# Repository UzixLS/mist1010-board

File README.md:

## MIST.1010
10x10cm PCB variant of [MIST FPGA](https://github.com/mist-devel/mist-board/wiki) project

[[More photos]](images/README.md)

Tech specs:
- EP3C25E144 FPGA
- 32/64Mb SDRAM
- VGA/RGB video output
- Composite video + audio output via 3.5 jack connector (raspberry-pi compatible pinout)
- 4xUSB ports for keyboard, mouse and joysticks
- 2xDB-9 ports for Amiga mouse and joysticks
- SD/microSD card slot
- RTC (clock) with battery
- Tape input / output
- ESP8266 WiFi module
- MIDI input and output (starting from rev.C)
- Type C (starting from rev.D) or MicroUSB power supply
- Board optimized for G738 and G706 cases

Some random photos: [link](https://cloud.err200.net/index.php/s/73TR85tYZkMm8Ax?path=%2Fmist1010)

### Changelog
* Rev.A - first revision. Please note the [errata](pcb/rev.A/ERRATA.txt).
* Rev.A1:
    * fixed all rev.A issues
    * LM3940IS-3.3 replaced to NCP1117-3.3
    * sound output circuit has been replaced with the original one from the MIST 1.3 circuit
    * C39, C40, C80 tantalum capacitors has been replaced by aluminum electrolytic capacitors
    * added ARM's "erase" testpoint
    * removed useless internal speaker
* Rev.A2:
	* C41, C68, C69 10uf ceramic capacitors has been replaced with 22uf tantalum
    * added C74 ceramic capacitor near ESP-01 module
* Rev.B:
    * added ESP-12E/F footprint (ESP-01 is still an option)
    * added MIDI input and output
    * removed U11 - AD724 encoder
    * added resistors-based CVBS (Y+C) video circuit
    * added JP4 solder jumper to disconnect CVBS circuit from 3.5mm jack
    * added U16 buffer with dedicated power source U17 for audio 1-bit DAC
    * added USB 2.54mm header
    * tuned SDRAM traces length for better match with MIST v1.3 PCB
    * changed U6 (attiny) footprint from DIP to SOIC
    * changed Y1 and Y2 footprints from THT to SMD
    * changed 1117-3.3 footprint from TO-252-2 to SOT-223-3
    * added U12 dedicated +3.3V power source for SD card and WiFi
    * 3mm front leds replaced by 5mm
    * R38 (VGA's +5V 0Ω resistor) has been replaced by solder jumper
    * changed tape header pinout
    * pcb corners are rounded now
    * experimental reset circuit based on MAX809
    * various changes in board layout
* Rev.C:
    * used USB Type C instead of Micro USB
    * PJ-320 3.5mm jack replaced by PJ-322
    * added solder jumper to select 3.5mm jack CVBS pinout
    * improved power distribution for FPGA chip
    * removed U16 buffer for DAC as it didn't bring any benefits
    * marked C27 and C28 as DNP
    * reverted to old reset circuit
    * various minor changes in board layout
* Rev.C1:
    * changed R47 from 220Ω to 1kΩ to reduce power led brightness
    * slightly moved C87 and C89

### Useful links
* MIST wiki: [link](https://github.com/mist-devel/mist-board/wiki)
* MIST cores and firmwares: [link](https://github.com/mist-devel/mist-binaries)

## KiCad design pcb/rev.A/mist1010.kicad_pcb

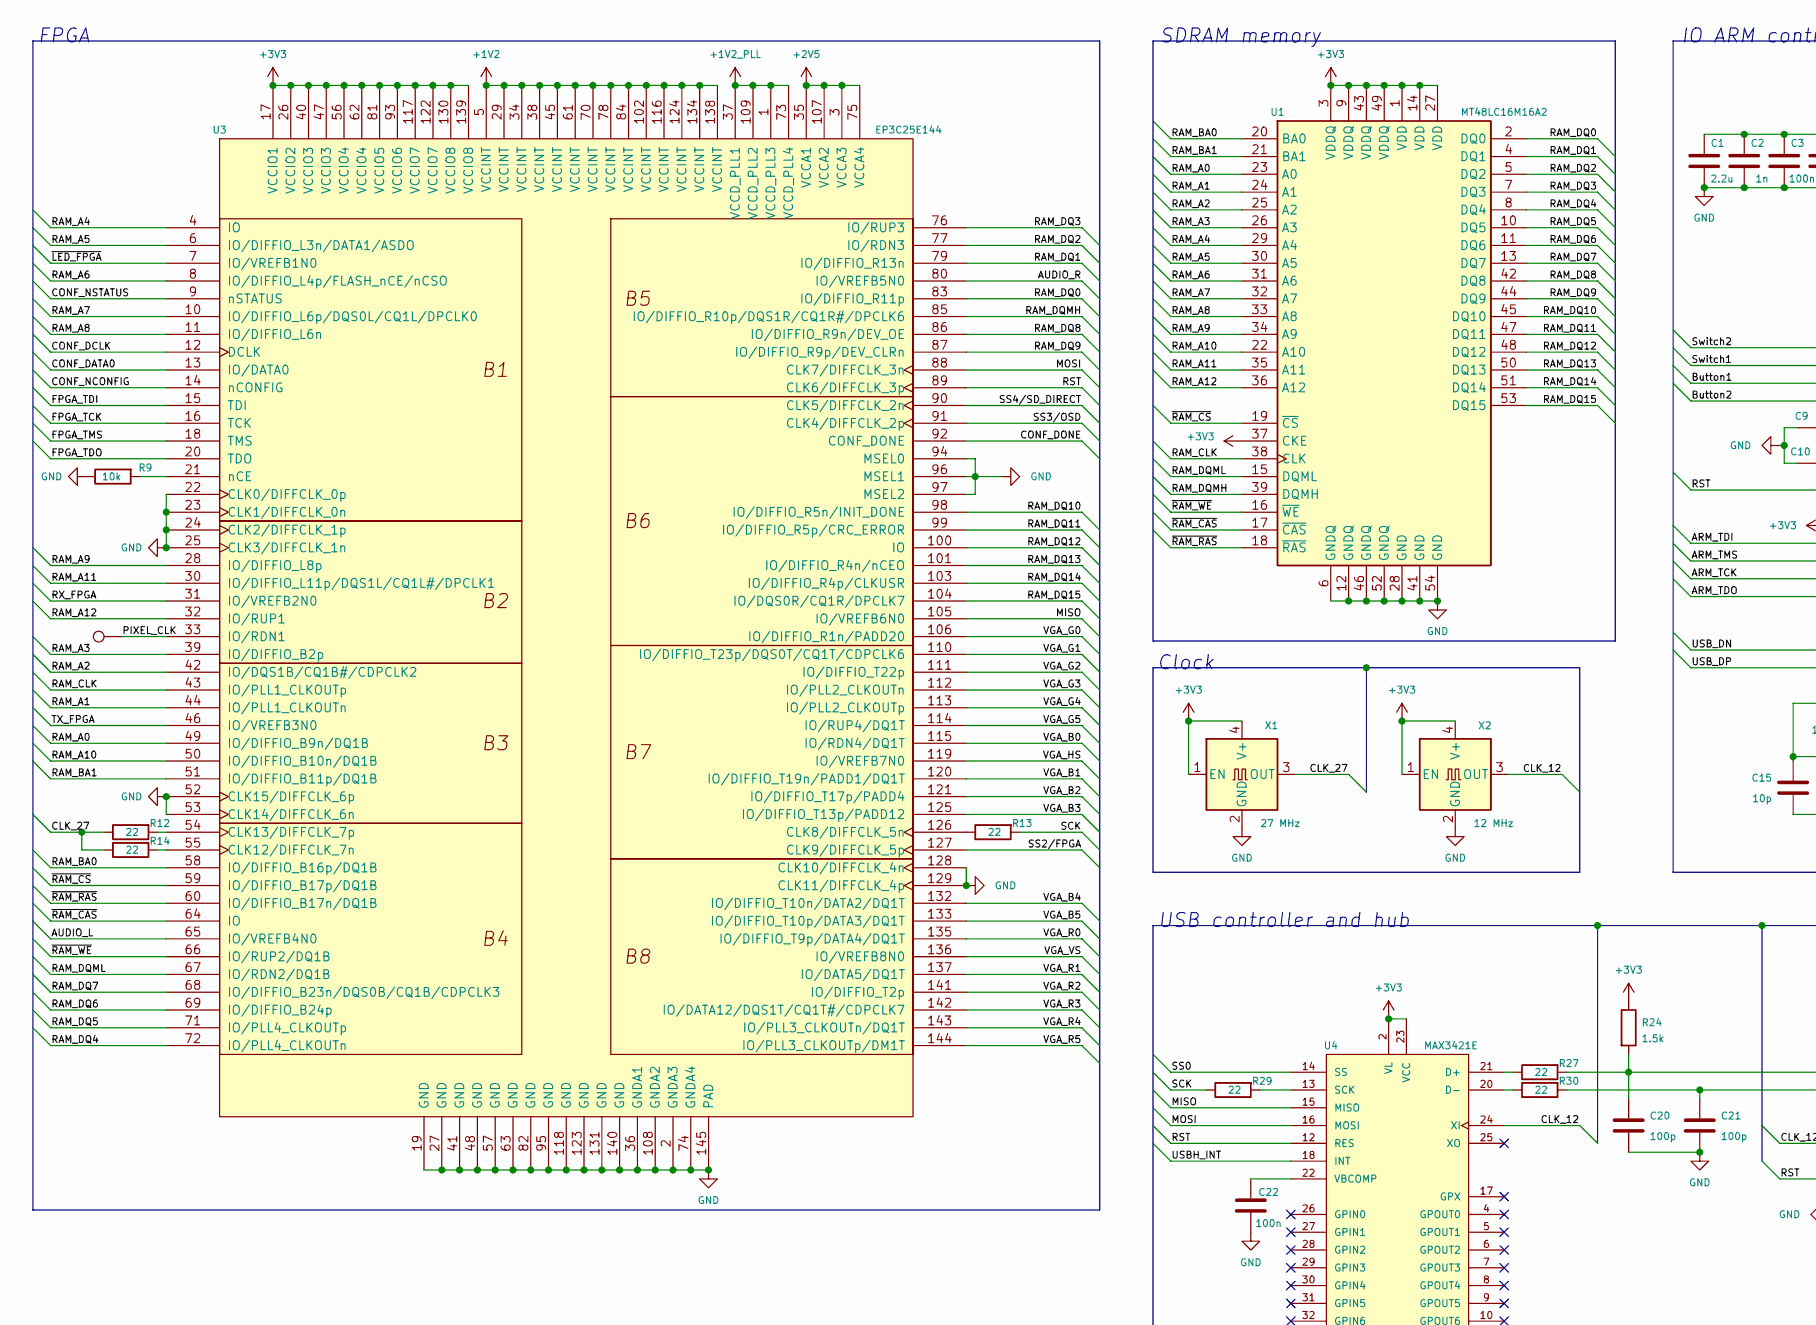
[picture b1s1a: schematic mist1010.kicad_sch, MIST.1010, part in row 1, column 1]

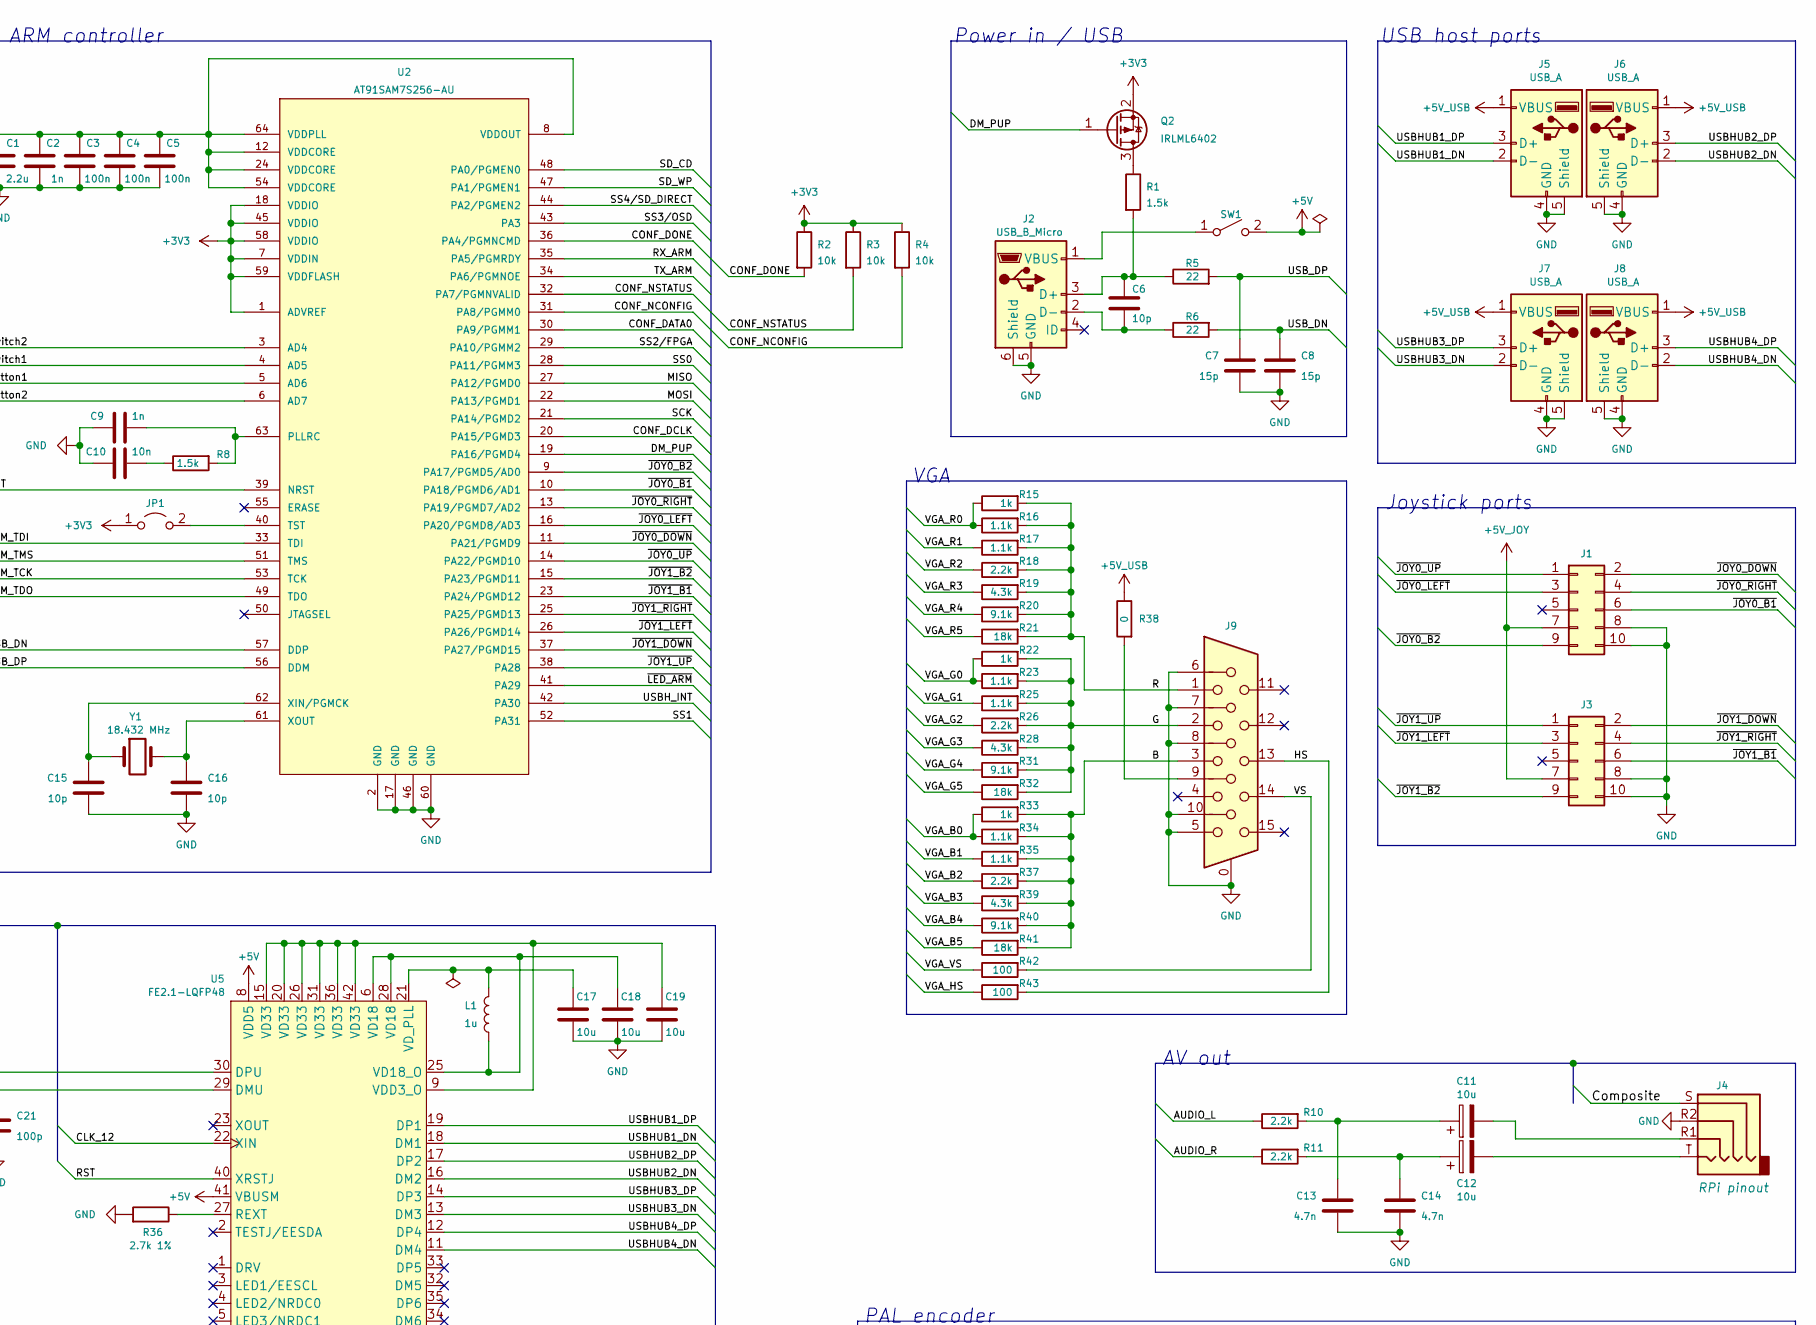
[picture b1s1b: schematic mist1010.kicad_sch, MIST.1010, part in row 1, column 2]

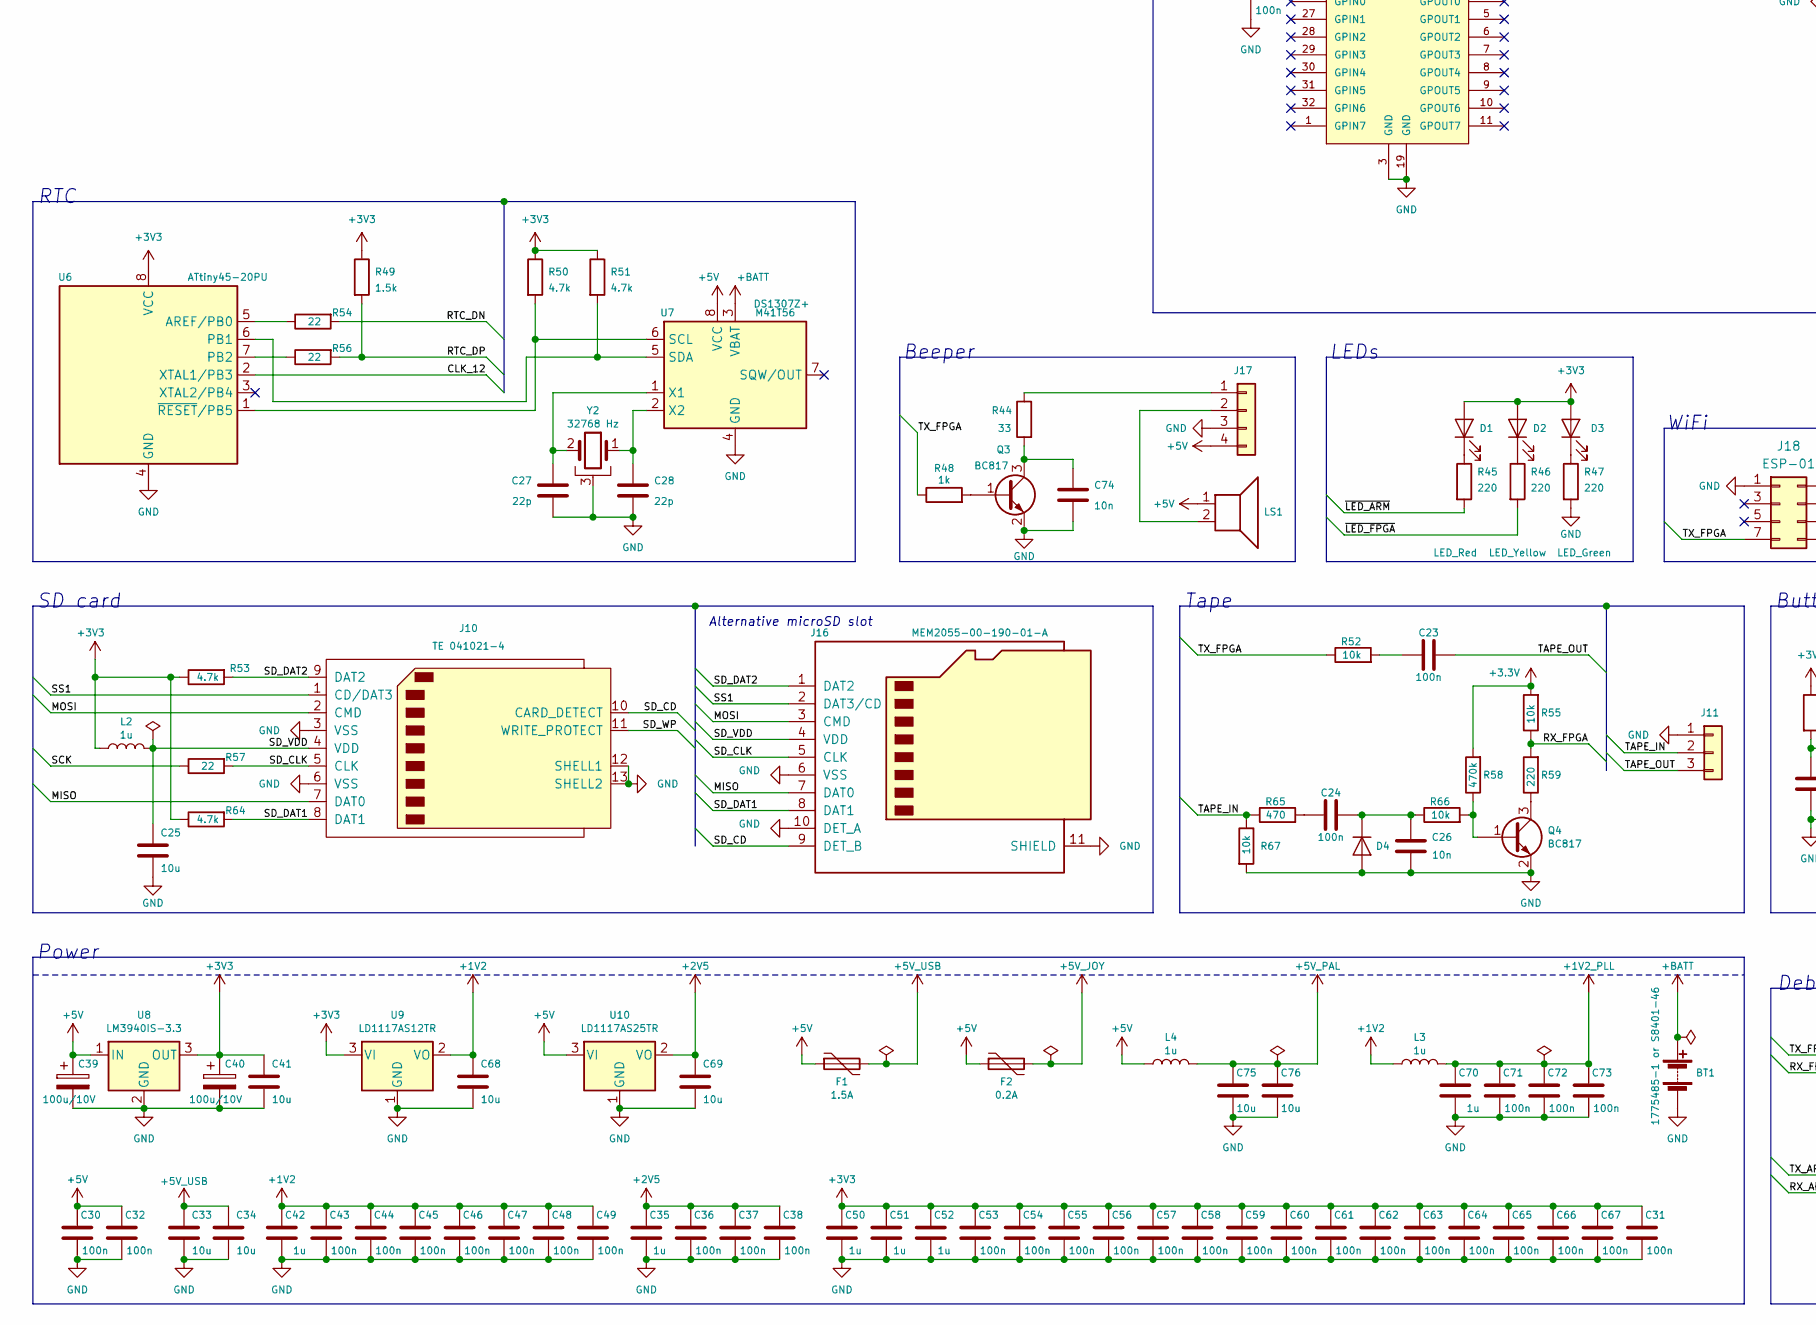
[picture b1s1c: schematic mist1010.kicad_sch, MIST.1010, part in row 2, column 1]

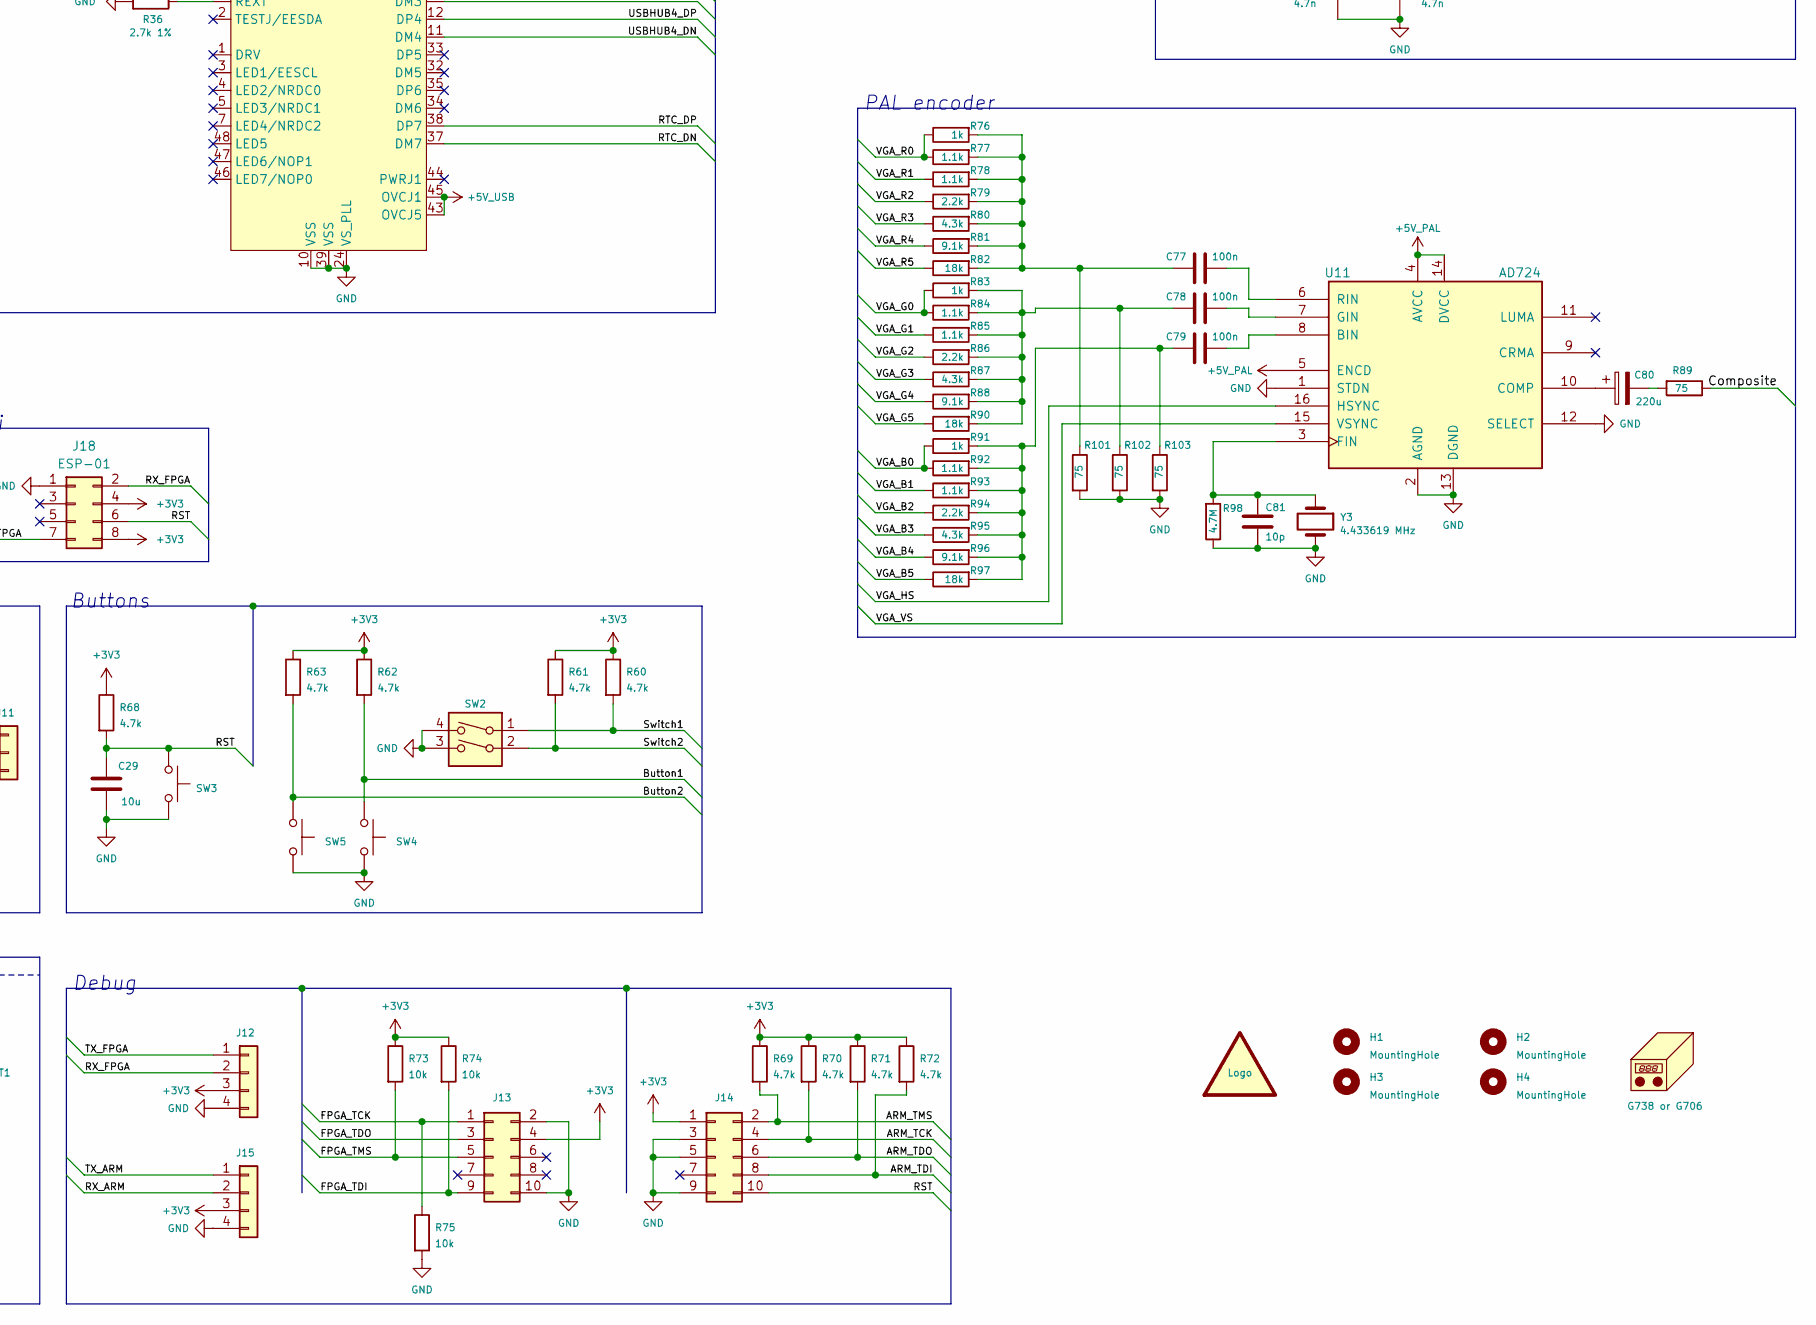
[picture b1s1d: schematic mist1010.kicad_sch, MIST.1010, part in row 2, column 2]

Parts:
BT1: 1775485-1 or S8401-46; CR2032V
C1: 2.2u; C_0805_2012Metric_Pad1.18x1.45mm_HandSolder
C2, C9: 1n; C_0603_1608Metric_Pad1.08x0.95mm_HandSolder
C3, C4, C5, C22, C23, C24, C30, C31, C32, C36, C37, C38, C43, C44, C45, C46, C47, C48, C49, C53, C54, C55, C56, C57, C58, C59, C60, C61, C62, C63, C64, C65, C66, C67, C71, C72, C73, C77, C78, C79: 100n; C_0603_1608Metric_Pad1.08x0.95mm_HandSolder
C6, C15, C16, C81: 10p; C_0603_1608Metric_Pad1.08x0.95mm_HandSolder
C7, C8: 15p; C_0603_1608Metric_Pad1.08x0.95mm_HandSolder
C10, C26, C74: 10n; C_0603_1608Metric_Pad1.08x0.95mm_HandSolder
C11, C12: 10u; CP_Elec_4x5.4
C13, C14: 4.7n; C_0603_1608Metric_Pad1.08x0.95mm_HandSolder
C17, C18, C19, C25, C29, C33, C34, C41, C68, C69, C75, C76: 10u; C_0805_2012Metric_Pad1.18x1.45mm_HandSolder
C20, C21: 100p; C_0603_1608Metric_Pad1.08x0.95mm_HandSolder
C27, C28: 22p; C_0603_1608Metric_Pad1.08x0.95mm_HandSolder
C35, C42, C50, C51, C52, C70: 1u; C_0603_1608Metric_Pad1.08x0.95mm_HandSolder
C39, C40: 100u/10V; CP_EIA-7343-31_Kemet-D_Pad2.25x2.55mm_HandSolder
C80: 220u; CP_EIA-7343-31_Kemet-D
D1: LED_Red; LED_D3.0mm_Horizontal_O1.27mm_Z6.0mm
D2: LED_Yellow; LED_D3.0mm_Horizontal_O1.27mm_Z6.0mm
D3: LED_Green; LED_D3.0mm_Horizontal_O1.27mm_Z6.0mm
D4: 1N4148W; D_SOD-123
F1: 1.5A; Fuse_1812_4532Metric_Pad1.30x3.40mm_HandSolder
F2: 0.2A; Fuse_1812_4532Metric_Pad1.30x3.40mm_HandSolder
H1, H2, H3, H4: MountingHole; MountingHole_3.2mm_M3_ISO14580
J1, J3, J13, J14: Conn_02x05_Odd_Even; PinHeader_2x05_P2.54mm_Vertical
J2: USB_B_Micro; USB_Micro-B_Molex-105017-0001
J4: PJ-320; PJ-320A_D
J5, J6, J7, J8: USB_A; USB_A_Wuerth_614004134726_Horizontal
J9: DB15_Female_HighDensity_MountingHoles; DSUB-15-HD_Female_Horizontal_P2.29x1.98mm_EdgePinOffset3.03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
J10: TE 041021-4; SD_TE_2041021-mod
J11: Conn_01x03; PinHeader_1x03_P2.54mm_Vertical
J12, J15, J17: Conn_01x04; PinHeader_1x04_P2.54mm_Vertical
J16: MEM2055-00-190-01-A; GCT-MEM2055-00-190-01-A
J18: ESP-01; PinSocket_2x04_P2.54mm_Vertical
JP1: Jumper_2_Open; PinHeader_1x02_P2.54mm_Vertical
L1, L2, L3, L4: 1u; L_0805_2012Metric_Pad1.15x1.40mm_HandSolder
LOGO1: graphic; black-mage-6.7x9.5
LS1: Speaker; Buzzer_12x9.5RM7.6
N1: G738 or G706
Q2: IRLML6402; SOT-23
Q3, Q4: BC817; SOT-23
R1, R8, R24, R49: 1.5k; R_0603_1608Metric_Pad0.98x0.95mm_HandSolder
R2, R3, R4, R9, R52, R55, R66, R67, R73, R74, R75: 10k; R_0603_1608Metric_Pad0.98x0.95mm_HandSolder
R5, R6, R12, R13, R14, R27, R29, R30, R54, R56, R57: 22; R_0603_1608Metric_Pad0.98x0.95mm_HandSolder
R10, R11, R18, R26, R37, R79, R86, R94: 2.2k; R_0603_1608Metric_Pad0.98x0.95mm_HandSolder
R15, R22, R33, R48, R76, R83, R91: 1k; R_0603_1608Metric_Pad0.98x0.95mm_HandSolder
R16, R17, R23, R25, R34, R35, R77, R78, R84, R85, R92, R93: 1.1k; R_0603_1608Metric_Pad0.98x0.95mm_HandSolder
R19, R28, R39, R80, R87, R95: 4.3k; R_0603_1608Metric_Pad0.98x0.95mm_HandSolder
R20, R31, R40, R81, R88, R96: 9.1k; R_0603_1608Metric_Pad0.98x0.95mm_HandSolder
R21, R32, R41, R82, R90, R97: 18k; R_0603_1608Metric_Pad0.98x0.95mm_HandSolder
R36: 2.7k 1%; R_0603_1608Metric_Pad0.98x0.95mm_HandSolder
R38: 0; R_0603_1608Metric_Pad0.98x0.95mm_HandSolder
R42, R43: 100; R_0603_1608Metric_Pad0.98x0.95mm_HandSolder
R44: 33; R_0805_2012Metric_Pad1.20x1.40mm_HandSolder
R45, R46, R47, R59: 220; R_0603_1608Metric_Pad0.98x0.95mm_HandSolder
R50, R51, R53, R60, R61, R62, R63, R64, R68, R69, R70, R71, R72: 4.7k; R_0603_1608Metric_Pad0.98x0.95mm_HandSolder
R58: 470k; R_0603_1608Metric_Pad0.98x0.95mm_HandSolder
R65: 470; R_0603_1608Metric_Pad0.98x0.95mm_HandSolder
R89, R101, R102, R103: 75; R_0603_1608Metric_Pad0.98x0.95mm_HandSolder
R98: 4.7M; R_0603_1608Metric_Pad0.98x0.95mm_HandSolder
SW1: Jumper / Pin header 1x2 Pitch=2.54mm; Molex_KK-254_AE-6410-02A_1x02_P2.54mm_Vertical
SW2: SW_DIP_x02; SW_DIP_SPSTx02_Slide_9.78x7.26mm_W7.62mm_P2.54mm
SW3, SW4, SW5: SW_Push; SW_Tactile_SPST_Angled_PTS645Vx58-2LFS
TP1: TestPoint; TestPoint_Pad_D1.0mm
U1: MT48LC16M16A2; TSOP-II-54_22.2x10.16mm_P0.8mm
U2: AT91SAM7S256-AU; TQFP-64_10x10mm_P0.5mm; MPN AT91SAM7S256-AU-001
U3: EP3C25E144; ALTERA-QFP-145
U4: MAX3421E; LQFP-32_5x5mm_P0.5mm
U5: FE2.1-LQFP48; LQFP-48_7x7mm_P0.5mm
U6: ATtiny45-20PU; DIP-8_W7.62mm
U7: DS1307Z+; SOIC-8_3.9x4.9mm_P1.27mm
U8: LM3940IS-3.3; TO-263-3_TabPin2
U9: LD1117AS12TR; SOT-223-3_TabPin2
U10: LD1117AS25TR; SOT-223-3_TabPin2
U11: AD724; SOIC-16W_7.5x10.3mm_P1.27mm
X1: 27 MHz; Oscillator_SMD_EuroQuartz_XO91-4Pin_7.0x5.0mm_HandSoldering
X2: 12 MHz; Oscillator_SMD_EuroQuartz_XO91-4Pin_7.0x5.0mm_HandSoldering
Y1: 18.432 MHz; Crystal_HC49-U_Vertical
Y2: 32768 Hz; Crystal_C38-LF_D3.0mm_L8.0mm_Horizontal_1EP_style2
Y3: 4.433619 MHz; Crystal_SMD_HC49-SD

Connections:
+1V2: C42.2, C43.2, C44.2, C45.2, C46.2, C47.2, C48.2, C49.2, C68.2, L3.1, U3.5 (VCCINT), U3.29 (VCCINT), U3.34 (VCCINT), U3.38 (VCCINT), U3.45 (VCCINT), U3.61 (VCCINT), U3.70 (VCCINT), U3.78 (VCCINT), U3.84 (VCCINT), U3.102 (VCCINT), U3.116 (VCCINT), U3.124 (VCCINT), U3.134 (VCCINT), U3.138 (VCCINT), U9.2 (VO)
+1V2_PLL: C70.2, C71.2, C72.2, C73.2, L3.2, U3.1 (VCCD_PLL3), U3.37 (VCCD_PLL1), U3.73 (VCCD_PLL4), U3.109 (VCCD_PLL2)
+2V5: C35.2, C36.2, C37.2, C38.2, C69.2, U3.3 (VCCA3), U3.35 (VCCA1), U3.75 (VCCA4), U3.107 (VCCA2), U10.2 (VO)
+5V: C30.2, C32.2, C39.1, F1.1, F2.1, J17.4, L4.1, LS1.1, SW1.2 (B), U5.8 (VDD5), U5.41 (VBUSM), U7.8 (VCC), U8.1 (IN), U10.3 (VI)
+5V_JOY: F2.2, J1.7, J3.7
+5V_PAL: C75.2, C76.2, L4.2, U11.4 (AVCC), U11.5 (ENCD), U11.14 (DVCC)
+5V_USB: C33.2, C34.2, F1.2, J5.1 (VBUS), J6.1 (VBUS), J7.1 (VBUS), J8.1 (VBUS), R38.1, U5.43 (OVCJ5), U5.45 (OVCJ1)
+BATT: BT1.1 (+), U7.3 (VBAT)
/ARM_TCK: J14.4, R70.2, U2.53 (TCK)
/ARM_TDI: J14.8, R72.2, U2.33 (TDI)
/ARM_TDO: J14.6, R71.2, U2.49 (TDO)
/ARM_TMS: J14.2, R69.2, U2.51 (TMS)
/AUDIO_L: R10.1, U3.65 (IO/VREFB4N0)
/AUDIO_R: R11.1, U3.80 (IO/VREFB5N0)
/B: J9.3, R33.2, R34.2, R35.2, R37.2, R39.2, R40.2, R41.2
/Button1: R62.2, SW4.1, U2.5 (AD6)
/Button2: R63.2, SW5.1, U2.6 (AD7)
/CLK_12: U4.24 (XI), U5.22 (XIN), U6.2 (XTAL1/PB3), X2.3 (OUT)
/CLK_27: R12.1, R14.1, X1.3 (OUT)
/CONF_DATA0: U2.30 (PA9/PGMM1), U3.13 (IO/DATA0)
/CONF_DCLK: U2.20 (PA15/PGMD3), U3.12 (DCLK)
/CONF_DONE: R2.2, U2.36 (PA4/PGMNCMD), U3.92 (CONF_DONE)
/CONF_NCONFIG: R4.2, U2.31 (PA8/PGMM0), U3.14 (nCONFIG)
/CONF_NSTATUS: R3.2, U2.32 (PA7/PGMNVALID), U3.9 (nSTATUS)
/Composite: J4.S, R89.1
/DM_PUP: Q2.1 (G), U2.19 (PA16/PGMD4)
/FPGA_TCK: J13.1, R75.1, U3.16 (TCK)
/FPGA_TDI: J13.9, R74.2, U3.15 (TDI)
/FPGA_TDO: J13.3, U3.20 (TDO)
/FPGA_TMS: J13.5, R73.2, U3.18 (TMS)
/G: J9.2, R22.2, R23.2, R25.2, R26.2, R28.2, R31.2, R32.2
/HS: J9.13, R43.2
/MISO: J10.7 (DAT0), J16.7 (DAT0), U2.27 (PA12/PGMD0), U3.105 (IO/VREFB6N0), U4.15 (MISO)
/MOSI: J10.2 (CMD), J16.3 (CMD), U2.22 (PA13/PGMD1), U3.88 (CLK7/DIFFCLK_3n), U4.16 (MOSI)
/PIXEL_CLK: TP1.1, U3.33 (IO/RDN1)
/R: J9.1, R15.2, R16.2, R17.2, R18.2, R19.2, R20.2, R21.2
/RAM_A0: U1.23 (A0), U3.49 (IO/DIFFIO_B9n/DQ1B)
/RAM_A1: U1.24 (A1), U3.44 (IO/PLL1_CLKOUTn)
/RAM_A2: U1.25 (A2), U3.42 (IO/DQS1B/CQ1B#/CDPCLK2)
/RAM_A3: U1.26 (A3), U3.39 (IO/DIFFIO_B2p)
/RAM_A4: U1.29 (A4), U3.4 (IO)
/RAM_A5: U1.30 (A5), U3.6 (IO/DIFFIO_L3n/DATA1/ASDO)
/RAM_A6: U1.31 (A6), U3.8 (IO/DIFFIO_L4p/FLASH_nCE/nCSO)
/RAM_A7: U1.32 (A7), U3.10 (IO/DIFFIO_L6p/DQS0L/CQ1L/DPCLK0)
/RAM_A8: U1.33 (A8), U3.11 (IO/DIFFIO_L6n)
/RAM_A9: U1.34 (A9), U3.28 (IO/DIFFIO_L8p)
/RAM_A10: U1.22 (A10), U3.50 (IO/DIFFIO_B10n/DQ1B)
/RAM_A11: U1.35 (A11), U3.30 (IO/DIFFIO_L11p/DQS1L/CQ1L#/DPCLK1)
/RAM_A12: U1.36 (A12), U3.32 (IO/RUP1)
/RAM_BA0: U1.20 (BA0), U3.58 (IO/DIFFIO_B16p/DQ1B)
/RAM_BA1: U1.21 (BA1), U3.51 (IO/DIFFIO_B11p/DQ1B)
/RAM_CLK: U1.38 (CLK), U3.43 (IO/PLL1_CLKOUTp)
/RAM_DQ0: U1.2 (DQ0), U3.83 (IO/DIFFIO_R11p)
/RAM_DQ1: U1.4 (DQ1), U3.79 (IO/DIFFIO_R13n)
/RAM_DQ2: U1.5 (DQ2), U3.77 (IO/RDN3)
/RAM_DQ3: U1.7 (DQ3), U3.76 (IO/RUP3)
/RAM_DQ4: U1.8 (DQ4), U3.72 (IO/PLL4_CLKOUTn)
/RAM_DQ5: U1.10 (DQ5), U3.71 (IO/PLL4_CLKOUTp)
/RAM_DQ6: U1.11 (DQ6), U3.69 (IO/DIFFIO_B24p)
/RAM_DQ7: U1.13 (DQ7), U3.68 (IO/DIFFIO_B23n/DQS0B/CQ1B/CDPCLK3)
/RAM_DQ8: U1.42 (DQ8), U3.86 (IO/DIFFIO_R9n/DEV_OE)
/RAM_DQ9: U1.44 (DQ9), U3.87 (IO/DIFFIO_R9p/DEV_CLRn)
/RAM_DQ10: U1.45 (DQ10), U3.98 (IO/DIFFIO_R5n/INIT_DONE)
/RAM_DQ11: U1.47 (DQ11), U3.99 (IO/DIFFIO_R5p/CRC_ERROR)
/RAM_DQ12: U1.48 (DQ12), U3.100 (IO)
/RAM_DQ13: U1.50 (DQ13), U3.101 (IO/DIFFIO_R4n/nCEO)
/RAM_DQ14: U1.51 (DQ14), U3.103 (IO/DIFFIO_R4p/CLKUSR)
/RAM_DQ15: U1.53 (DQ15), U3.104 (IO/DQS0R/CQ1R/DPCLK7)
/RAM_DQMH: U1.39 (DQMH), U3.85 (IO/DIFFIO_R10p/DQS1R/CQ1R#/DPCLK6)
/RAM_DQML: U1.15 (DQML), U3.67 (IO/RDN2/DQ1B)
/RST: C29.2, J14.10, J18.6, R68.2, SW3.1, U2.39 (NRST), U3.89 (CLK6/DIFFCLK_3p), U4.12 (RES), U5.40 (XRSTJ)
/RTC_DN: R54.2, U5.37 (DM7)
/RTC_DP: R49.2, R56.2, U5.38 (DP7)
/RX_ARM: J15.2, U2.35 (PA5/PGMRDY)
/RX_FPGA: J12.2, J18.2, R55.1, R59.2, U3.31 (IO/VREFB2N0)
/SCK: R13.2, R29.1, R57.1, U2.21 (PA14/PGMD2)
/SD_CD: J10.10 (CARD_DETECT), J16.9 (DET_B), U2.48 (PA0/PGMEN0)
/SD_CLK: J10.5 (CLK), J16.5 (CLK), R57.2
/SD_DAT1: J10.8 (DAT1), J16.8 (DAT1), R64.2
/SD_DAT2: J10.9 (DAT2), J16.1 (DAT2), R53.2
/SD_VDD: C25.2, J10.4 (VDD), J16.4 (VDD), L2.2
/SD_WP: J10.11 (WRITE_PROTECT), U2.47 (PA1/PGMEN1)
/SS0: U2.28 (PA11/PGMM3), U4.14 (SS)
/SS1: J10.1 (CD/DAT3), J16.2 (DAT3/CD), U2.52 (PA31)
/SS2/FPGA: U2.29 (PA10/PGMM2), U3.127 (CLK9/DIFFCLK_5p)
/SS3/OSD: U2.43 (PA3), U3.91 (CLK4/DIFFCLK_2p)
/SS4/SD_DIRECT: U2.44 (PA2/PGMEN2), U3.90 (CLK5/DIFFCLK_2n)
/Switch1: R60.2, SW2.1, U2.4 (AD5)
/Switch2: R61.2, SW2.2, U2.3 (AD4)
/TAPE_IN: J11.2, R65.1, R67.1
/TAPE_OUT: C23.1, J11.3
/TX_ARM: J15.1, U2.34 (PA6/PGMNOE)
/TX_FPGA: J12.1, J18.7, R48.1, R52.1, U3.46 (IO/VREFB3N0)
/USBHUB1_DN: J5.2 (D-), U5.18 (DM1)
/USBHUB1_DP: J5.3 (D+), U5.19 (DP1)
/USBHUB2_DN: J6.2 (D-), U5.16 (DM2)
/USBHUB2_DP: J6.3 (D+), U5.17 (DP2)
/USBHUB3_DN: J7.2 (D-), U5.13 (DM3)
/USBHUB3_DP: J7.3 (D+), U5.14 (DP3)
/USBHUB4_DN: J8.2 (D-), U5.11 (DM4)
/USBHUB4_DP: J8.3 (D+), U5.12 (DP4)
/USBH_INT: U2.42 (PA30), U4.18 (INT)
/USB_DN: C8.1, R6.2, U2.57 (DDP)
/USB_DP: C7.1, R5.2, U2.56 (DDM)
/VGA_B0: R33.1, R34.1, R91.1, R92.1, U3.115 (IO/RDN4/DQ1T)
/VGA_B1: R35.1, R93.1, U3.120 (IO/DIFFIO_T19n/PADD1/DQ1T)
/VGA_B2: R37.1, R94.1, U3.121 (IO/DIFFIO_T17p/PADD4)
/VGA_B3: R39.1, R95.1, U3.125 (IO/DIFFIO_T13p/PADD12)
/VGA_B4: R40.1, R96.1, U3.132 (IO/DIFFIO_T10n/DATA2/DQ1T)
/VGA_B5: R41.1, R97.1, U3.133 (IO/DIFFIO_T10p/DATA3/DQ1T)
/VGA_G0: R22.1, R23.1, R83.1, R84.1, U3.106 (IO/DIFFIO_R1n/PADD20)
/VGA_G1: R25.1, R85.1, U3.110 (IO/DIFFIO_T23p/DQS0T/CQ1T/CDPCLK6)
/VGA_G2: R26.1, R86.1, U3.111 (IO/DIFFIO_T22p)
/VGA_G3: R28.1, R87.1, U3.112 (IO/PLL2_CLKOUTn)
/VGA_G4: R31.1, R88.1, U3.113 (IO/PLL2_CLKOUTp)
/VGA_G5: R32.1, R90.1, U3.114 (IO/RUP4/DQ1T)
/VGA_HS: R43.1, U3.119 (IO/VREFB7N0), U11.16 (HSYNC)
/VGA_R0: R15.1, R16.1, R76.1, R77.1, U3.135 (IO/DIFFIO_T9p/DATA4/DQ1T)
/VGA_R1: R17.1, R78.1, U3.137 (IO/DATA5/DQ1T)
/VGA_R2: R18.1, R79.1, U3.141 (IO/DIFFIO_T2p)
/VGA_R3: R19.1, R80.1, U3.142 (IO/DATA12/DQS1T/CQ1T#/CDPCLK7)
/VGA_R4: R20.1, R81.1, U3.143 (IO/PLL3_CLKOUTn/DQ1T)
/VGA_R5: R21.1, R82.1, U3.144 (IO/PLL3_CLKOUTp/DM1T)
/VGA_VS: R42.1, U3.136 (IO/VREFB8N0), U11.15 (VSYNC)
/VS: J9.14, R42.2
/~JOY0_B1: J1.6, U2.10 (PA18/PGMD6/AD1)
/~JOY0_B2: J1.9, U2.9 (PA17/PGMD5/AD0)
/~JOY0_DOWN: J1.2, U2.11 (PA21/PGMD9)
/~JOY0_LEFT: J1.3, U2.16 (PA20/PGMD8/AD3)
/~JOY0_RIGHT: J1.4, U2.13 (PA19/PGMD7/AD2)
/~JOY0_UP: J1.1, U2.14 (PA22/PGMD10)
/~JOY1_B1: J3.6, U2.23 (PA24/PGMD12)
/~JOY1_B2: J3.9, U2.15 (PA23/PGMD11)
/~JOY1_DOWN: J3.2, U2.37 (PA27/PGMD15)
/~JOY1_LEFT: J3.3, U2.26 (PA26/PGMD14)
/~JOY1_RIGHT: J3.4, U2.25 (PA25/PGMD13)
/~JOY1_UP: J3.1, U2.38 (PA28)
/~LED_ARM: R45.2, U2.41 (PA29)
/~LED_FPGA: R46.2, U3.7 (IO/VREFB1N0)
/~RAM_CAS: U1.17 (~CAS), U3.64 (IO)
/~RAM_CS: U1.19 (~CS), U3.59 (IO/DIFFIO_B17p/DQ1B)
/~RAM_RAS: U1.18 (~RAS), U3.60 (IO/DIFFIO_B17n/DQ1B)
/~RAM_WE: U1.16 (~WE), U3.66 (IO/RUP2/DQ1B)
GND: BT1.2 (-), C1.1, C2.1, C3.1, C4.1, C5.1, C7.2, C8.2, C9.2, C10.2, C13.2, C14.2, C15.2, C16.2, C17.1, C18.1, C19.1, C20.2, C21.2, C22.1, C25.1, C26.2, C27.2, C28.2, C29.1, C30.1, C31.1, C32.1, C33.1, C34.1, C35.1, C36.1, C37.1, C38.1, C39.2, C40.2, C41.1, C42.1, C43.1, C44.1, C45.1, C46.1, C47.1, C48.1, C49.1, C50.1, C51.1, C52.1, C53.1, C54.1, C55.1, C56.1, C57.1, C58.1, C59.1, C60.1, C61.1, C62.1, C63.1, C64.1, C65.1, C66.1, C67.1, C68.1, C69.1, C70.1, C71.1, C72.1, C73.1, C74.2, C75.1, C76.1, C81.2, D4.2 (A), J1.8, J1.10, J2.5 (GND), J2.6 (Shield), J3.8, J3.10, J4.R2, J5.4 (GND), J5.5 (Shield), J6.4 (GND), J6.5 (Shield), J7.4 (GND), J7.5 (Shield), J8.4 (GND), J8.5 (Shield), J9.0, J9.5, J9.6, J9.7, J9.8, J9.10, J10.3 (VSS), J10.6 (VSS), J10.12 (SHELL1), J10.13 (SHELL2), J11.1, J12.4, J13.2, J13.10, J14.3, J14.5, J14.9, J15.4, J16.6 (VSS), J16.10 (DET_A), J16.11 (SHIELD), J17.3, J18.1, Q3.2 (E), Q4.2 (E), R9.1, R36.2, R47.2, R67.2, R75.2, R98.1, R101.2, R102.2, R103.2, SW2.3, SW2.4, SW3.2, SW4.2, SW5.2, U1.6 (GNDQ), U1.12 (GNDQ), U1.28 (GND), U1.41 (GND), U1.46 (GNDQ), U1.52 (GNDQ), U1.54 (GND), U2.2 (GND), U2.17 (GND), U2.46 (GND), U2.60 (GND), U3.2 (GNDA3), U3.19 (GND), U3.22 (CLK0/DIFFCLK_0p), U3.23 (CLK1/DIFFCLK_0n), U3.24 (CLK2/DIFFCLK_1p), U3.25 (CLK3/DIFFCLK_1n), U3.27 (GND), U3.36 (GNDA1), U3.41 (GND), U3.48 (GND), U3.52 (CLK15/DIFFCLK_6p), U3.53 (CLK14/DIFFCLK_6n), U3.57 (GND), U3.63 (GND), U3.74 (GNDA4), U3.82 (GND), U3.94 (MSEL0), U3.95 (GND), U3.96 (MSEL1), U3.97 (MSEL2), U3.108 (GNDA2), U3.118 (GND), U3.123 (GND), U3.128 (CLK10/DIFFCLK_4n), U3.129 (CLK11/DIFFCLK_4p)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
unnamed: C1.2, C2.2, C3.2, C4.2, C5.2, U2.8 (VDDOUT), U2.12 (VDDCORE), U2.24 (VDDCORE), U2.54 (VDDCORE), U2.64 (VDDPLL)
unnamed: C6.1, J2.3 (D+), R1.2, R5.1
unnamed: C6.2, J2.2 (D-), R6.1
unnamed: C9.1, R8.2, U2.63 (PLLRC)
unnamed: C10.1, R8.1
unnamed: C11.1, C13.1, R10.2
unnamed: C11.2, J4.R1
unnamed: C12.1, C14.1, R11.2
unnamed: C12.2, J4.T
unnamed: C15.1, U2.62 (XIN/PGMCK), Y1.1
unnamed: C16.1, U2.61 (XOUT), Y1.2
unnamed: C17.2, L1.2, U5.21 (VD_PLL)
unnamed: C18.2, L1.1, U5.6 (VD18), U5.25 (VD18_O), U5.28 (VD18)
unnamed: C19.2, U5.9 (VDD3_O), U5.15 (VD33), U5.20 (VD33), U5.26 (VD33), U5.31 (VD33), U5.36 (VD33), U5.42 (VD33)
unnamed: C20.1, R24.2, R27.2, U5.30 (DPU)
unnamed: C21.1, R30.2, U5.29 (DMU)
unnamed: C22.2, U4.22 (VBCOMP)
unnamed: C23.2, R52.2
unnamed: C24.1, C26.1, D4.1 (K), R66.1
unnamed: C24.2, R65.2
unnamed: C27.1, U7.1 (X1), Y2.2
unnamed: C28.1, U7.2 (X2), Y2.1
unnamed: C74.1, Q3.3 (C), R44.2
unnamed: C77.1, U11.6 (RIN)
unnamed: C77.2, R76.2, R77.2, R78.2, R79.2, R80.2, R81.2, R82.2, R101.1
unnamed: C78.1, U11.7 (GIN)
unnamed: C78.2, R83.2, R84.2, R85.2, R86.2, R87.2, R88.2, R90.2, R102.1
unnamed: C79.1, U11.8 (BIN)
unnamed: C79.2, R91.2, R92.2, R93.2, R94.2, R95.2, R96.2, R97.2, R103.1
unnamed: C80.1, U11.10 (COMP)
unnamed: C80.2, R89.2
unnamed: C81.1, R98.2, U11.3 (FIN), Y3.1
unnamed: D1.1 (K), R45.1
unnamed: D2.1 (K), R46.1
unnamed: D3.1 (K), R47.1
unnamed: J2.1 (VBUS), SW1.1 (A)
unnamed: J9.9, R38.2
unnamed: J17.1, R44.1
unnamed: J17.2, LS1.2
unnamed: JP1.2 (B), U2.40 (TST)
unnamed: Q2.3 (D), R1.1
unnamed: Q3.1 (B), R48.2
unnamed: Q4.1 (B), R58.1, R66.2
unnamed: Q4.3 (C), R59.1
unnamed: R9.2, U3.21 (nCE)
unnamed: R12.2, U3.54 (CLK13/DIFFCLK_7p)
unnamed: R13.1, U3.126 (CLK8/DIFFCLK_5n)
unnamed: R14.2, U3.55 (CLK12/DIFFCLK_7n)
unnamed: R27.1, U4.21 (D+)
unnamed: R29.2, U4.13 (SCK)
unnamed: R30.1, U4.20 (D-)
unnamed: R36.1, U5.27 (REXT)
unnamed: R50.2, U6.1 (~RESET~/PB5), U7.6 (SCL)
unnamed: R51.2, U6.6 (PB1), U7.5 (SDA)
unnamed: R54.1, U6.5 (AREF/PB0)
unnamed: R56.1, U6.7 (PB2)

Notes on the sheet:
RTC
FPGA
Power
SD card
Alternative microSD slot
Beeper
Clock
Tape
SDRAM memory
LEDs
USB controller and hub
WiFi
Debug
Buttons
IO ARM controller
VGA
PAL encoder
Power in / USB
AV out
Joystick ports
USB host ports

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
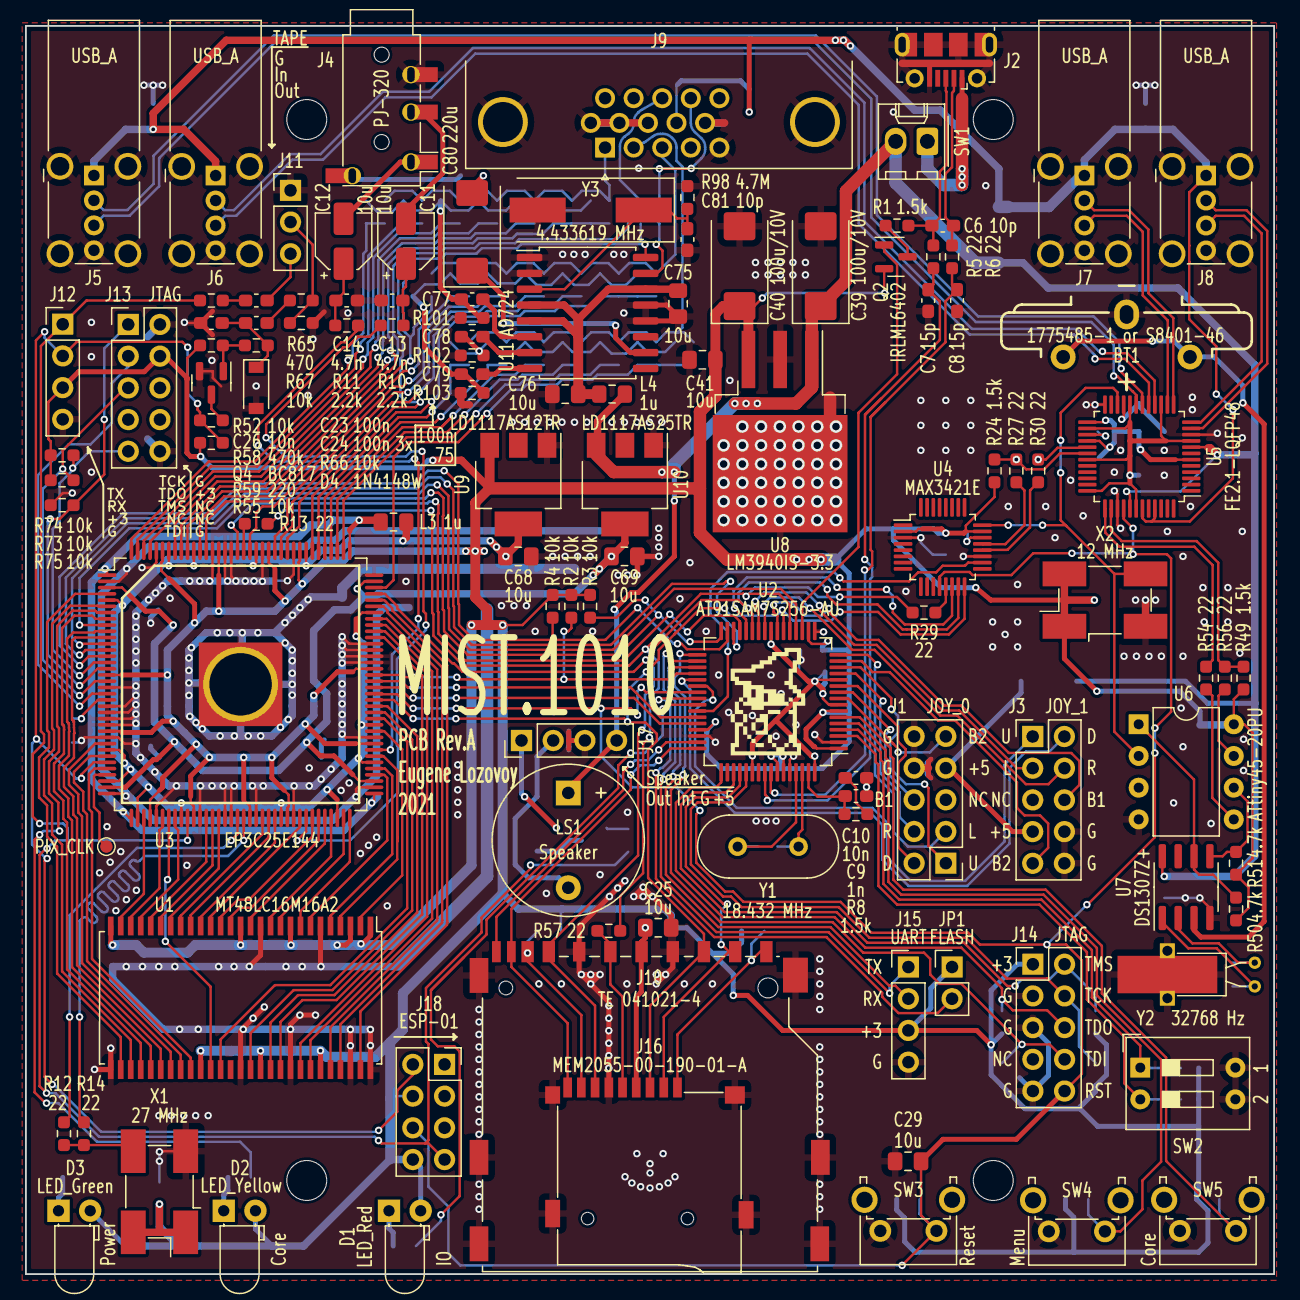
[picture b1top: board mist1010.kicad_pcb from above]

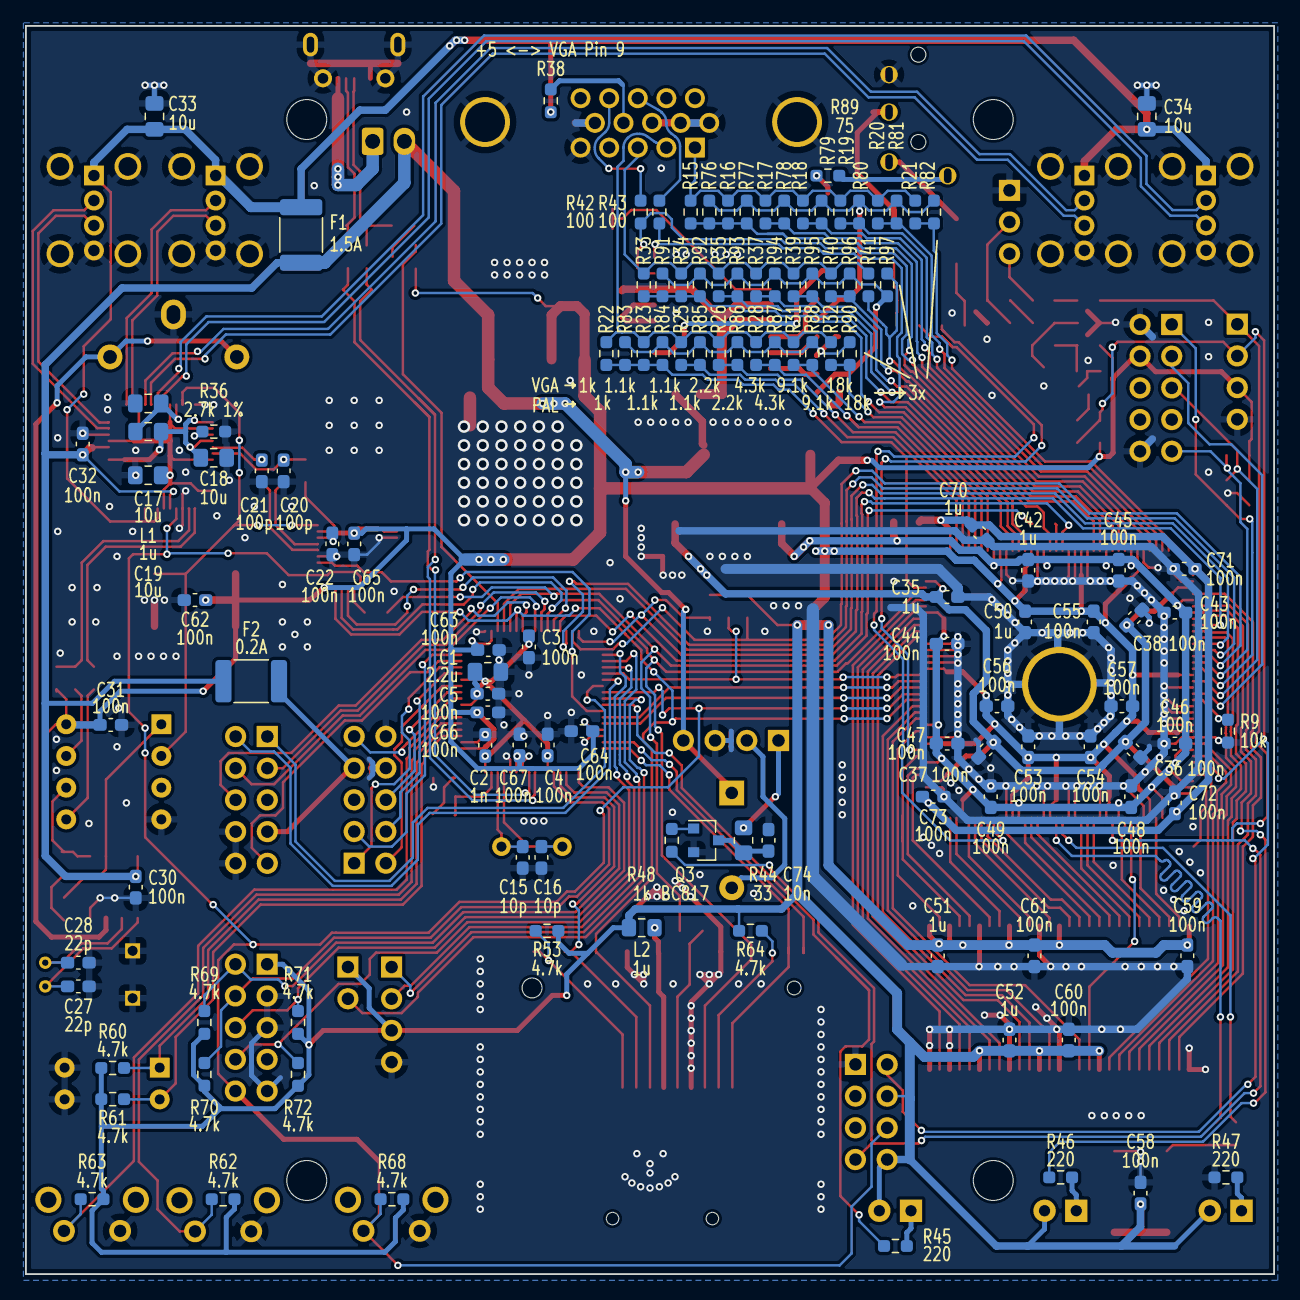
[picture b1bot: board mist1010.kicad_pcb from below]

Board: 2 copper layers, 100.0 x 100.0 mm, 242 parts (124 on the bottom side), 201 nets.
